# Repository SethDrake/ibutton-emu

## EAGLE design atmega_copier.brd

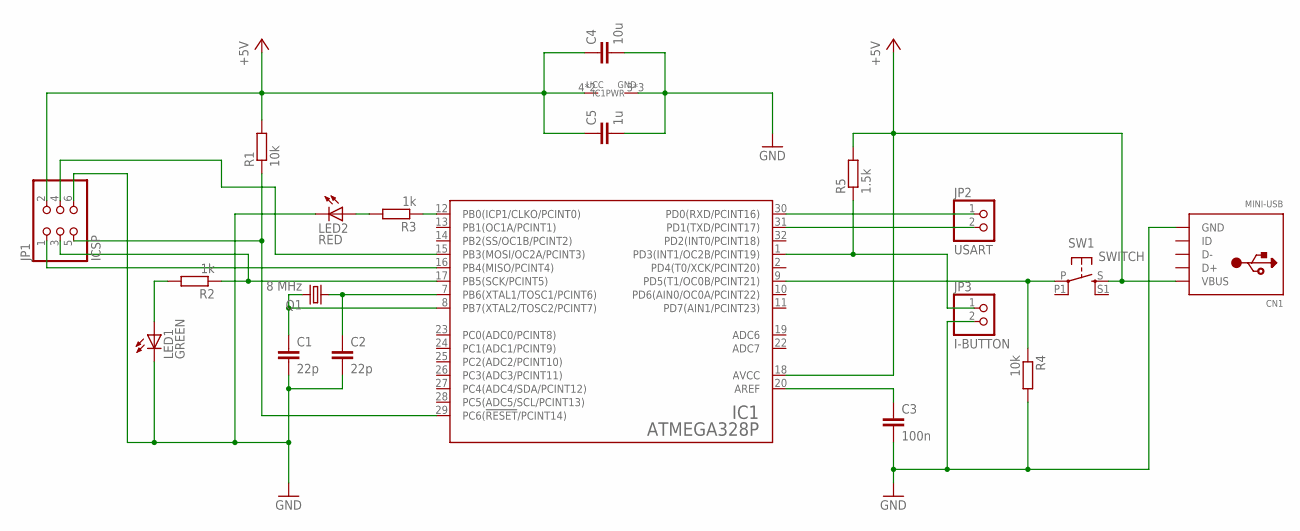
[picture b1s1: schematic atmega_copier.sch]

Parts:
C1, C2: 22p; C0805
C3: 100n; C0805
C4: 10u; C0805
C5: 1u; C0805
CN1: MINI-USB; USB-MINIB
IC1: ATMEGA328P; TQFP32-08
JP1: ICSP; 2X03
JP2: USART; 1X02
JP3: I-BUTTON; 1X02
LED1: GREEN; SML0805
LED2: RED; SML0805
Q1: 8 MHz; HC49UP
R1, R4: 10k; R0805
R2, R3: 1k; R0805
R5: 1.5k; R0805
SW1: SWITCH; BT4.5X4.5

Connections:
+5V: C4.1, C5.1, CN1.VBUS, IC1.4 (UCC), IC1.6 (UCC), IC1.18 (AVCC), JP1.2, R1.2, R5.2, SW1.S
AREF: C3.1, IC1.20 (AREF)
GND: C1.2, C2.2, C3.2, C4.2, C5.2, CN1.GND, IC1.3 (GND), IC1.5 (GND), IC1.21 (GND), JP1.6, JP3.2, LED1.C, LED2.C, R4.2
KEY: IC1.9 (PD5(T1/OC0B/PCINT21)), R4.1, SW1.P
MISO: IC1.16 (PB4(MISO/PCINT4)), JP1.1
MOSI: IC1.15 (PB3(MOSI/OC2A/PCINT3)), JP1.4
unnamed: IC1.1 (PD3(INT1/OC2B/PCINT19)), JP3.1, R5.1
unnamed: LED1.A, R2.2
unnamed: LED2.A, R3.2
RED_LED: IC1.12 (PB0(ICP1/CLKO/PCINT0)), R3.1
RESET: IC1.29 (PC6(!RESET!/PCINT14)), JP1.5, R1.1
RXD: IC1.30 (PD0(RXD/PCINT16)), JP2.1
SCK: IC1.17 (PB5(SCK/PCINT5)), JP1.3, R2.1
TXD: IC1.31 (PD1(TXD/PCINT17)), JP2.2
XTAL1: C2.1, IC1.7 (PB6(XTAL1/TOSC1/PCINT6)), Q1.1
XTAL2: C1.1, IC1.8 (PB7(XTAL2/TOSC2/PCINT7)), Q1.2

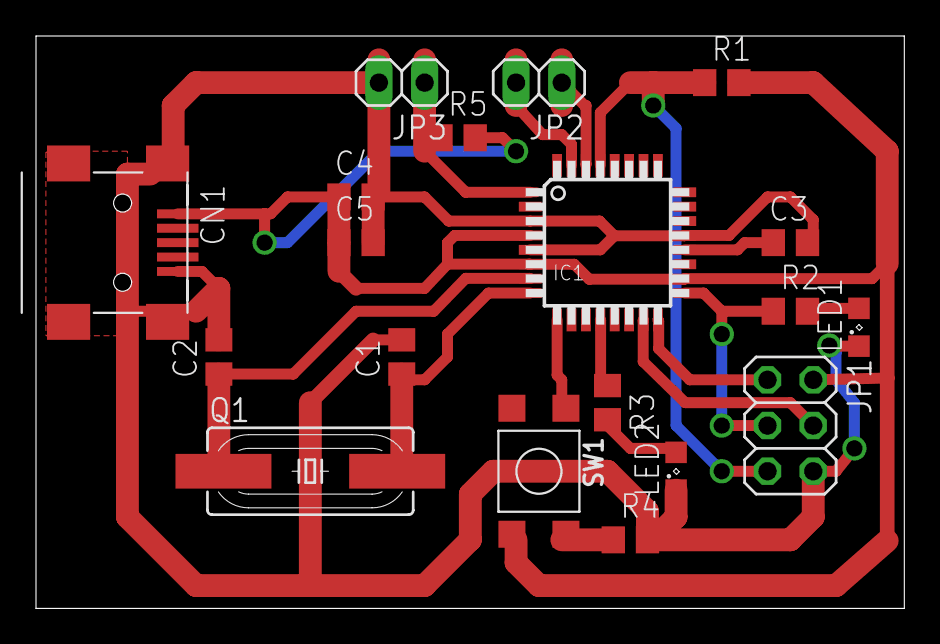
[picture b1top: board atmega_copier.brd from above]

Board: 2 copper layers, 48.2 x 31.8 mm, 19 parts (0 on the bottom side), 16 nets.

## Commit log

2018-11-03 reader/copier in progress..
2018-11-03 reader/copier in progress
2018-11-06 stm8s code in progress
2018-12-08 in progress..
2018-12-09 hw in progress
2018-12-10 sw in progress
2018-12-10 v1.0 completed
